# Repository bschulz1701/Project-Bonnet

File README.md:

# Project-Bonnet
Compact, self contained, multi-point voltage logger/monitor. Designed for use as a testing device.

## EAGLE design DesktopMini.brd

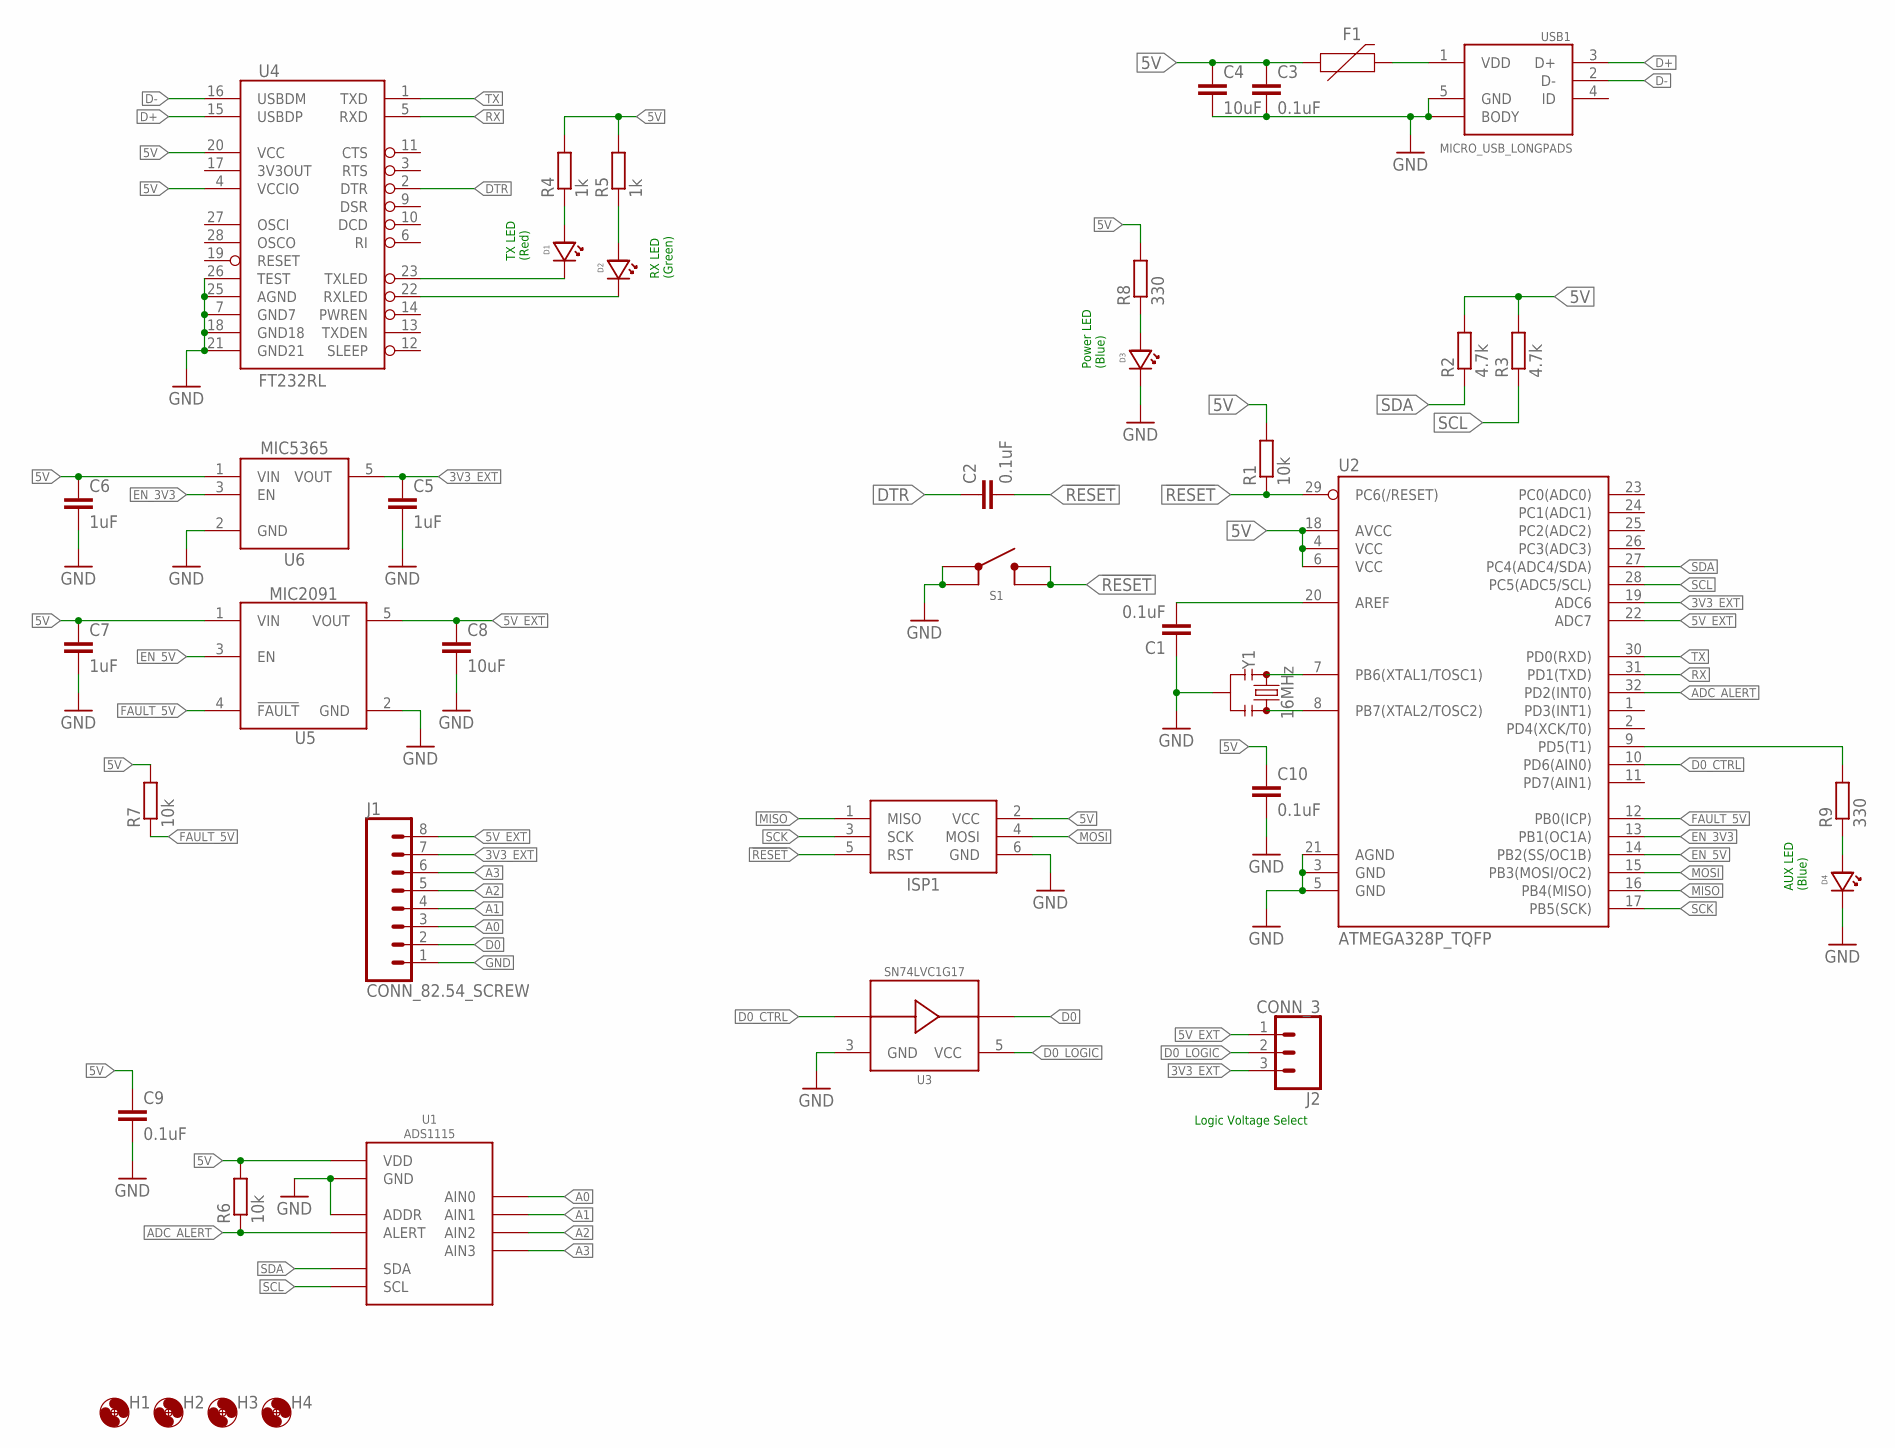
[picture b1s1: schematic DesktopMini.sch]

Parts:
C1, C2, C3, C9, C10: 0.1uF; C0603
C4, C8: 10uF; C0805
C5, C6, C7: 1uF; C0603
D1: LEDRED0603; LED_0603
D2: LEDGREEN0603; LED_0603
D3, D4: LEDBLUE0603; LED_0603
F1: PPTC_HALF-AMP; 1206
H1, H2, H3, H4: MOUNTING_HOLE4_NP; 4_40
ISP1: AVRISP-6; AVRISP
J1: CONN_82.54_SCREW; 1X08_SCREW
J2: CONN_3; 1X03
R1, R6, R7: 10k; R0603
R2, R3: 4.7k; R0603
R4, R5: 1k; R0603
R8, R9: 330; R0603
S1: BUTTON6X6; SWITCH_6MM
U1: ADS1115; VSSOP_10
U2: ATMEGA328P_TQFP; TQFP32-08
U3: SN74LVC1G17DCK; DCK_R-PDSO-G5
U4: FT232RL; SSOP28DB
U5: MIC2091; SOT23-5
U6: MIC53653.3SC70; DCK_R-PDSO-G5
USB1: MICRO_USB_LONGPADS; 10118194-0001LF_10118194-0001LF_LONGER_PADS
Y1: 16MHz; RESONATOR-SMD-3.2X1.3

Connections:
3V3_EXT: C5.1, J1.7, J2.3, U2.19 (ADC6), U6.5 (VOUT)
5V: C3.1, C4.1, C6.1, C7.1, C9.1, C10.1, F1.1, ISP1.2 (VCC), R1.2, R2.2, R3.2, R4.2, R5.2, R6.2, R7.2, R8.2, U1.8 (VDD), U2.4 (VCC), U2.6 (VCC), U2.18 (AVCC), U4.4 (VCCIO), U4.20 (VCC), U5.1 (VIN), U6.1 (VIN)
5V_EXT: C8.1, J1.8, J2.1, U2.22 (ADC7), U5.5 (VOUT)
!RESET: C2.2, ISP1.5 (RST), R1.1, S1.3, S1.4, U2.29 (PC6(/RESET))
A0: J1.3, U1.4 (AIN0)
A1: J1.4, U1.5 (AIN1)
A2: J1.5, U1.6 (AIN2)
A3: J1.6, U1.7 (AIN3)
ADC_ALERT: R6.1, U1.2 (ALERT), U2.32 (PD2(INT0))
AUX_LED: R9.2, U2.9 (PD5(T1))
D0: J1.2, U3.4 (Y)
D0_CTRL: U2.10 (PD6(AIN0)), U3.2 (A)
D0_LOGIC: J2.2, U3.5 (VCC)
D+: U4.15 (USBDP), USB1.3 (D+)
D-: U4.16 (USBDM), USB1.2 (D-)
DTR: C2.1, U4.2 (DTR)
EN_3V3: U2.13 (PB1(OC1A)), U6.3 (EN)
EN_5V: U2.14 (PB2(SS/OC1B)), U5.3 (EN)
FAULT_5V: R7.1, U2.12 (PB0(ICP)), U5.4 (!FAULT)
GND: C1.1, C3.2, C4.2, C5.2, C6.2, C7.2, C8.2, C9.2, C10.2, D3.CATHODE, D4.CATHODE, ISP1.6 (GND), J1.1, S1.1, S1.2, U1.1 (ADDR), U1.3 (GND), U2.3 (GND), U2.5 (GND), U2.21 (AGND), U3.3 (GND), U4.7 (GND7), U4.18 (GND18), U4.21 (GND21), U4.25 (AGND), U4.26 (TEST), U5.2 (GND), U6.2 (GND), USB1.5 (GND), USB1.BODY@1 (BODY), USB1.BODY@2 (BODY), USB1.BODY@3 (BODY), USB1.BODY@4 (BODY), USB1.BODY@7 (BODY), USB1.BODY@8 (BODY), Y1.2
MISO: ISP1.1 (MISO), U2.16 (PB4(MISO))
MOSI: ISP1.4 (MOSI), U2.15 (PB3(MOSI/OC2))
unnamed: U2.7 (PB6(XTAL1/TOSC1)), Y1.1
unnamed: U2.8 (PB7(XTAL2/TOSC2)), Y1.3
unnamed: C1.2, U2.20 (AREF)
unnamed: D1.ANODE, R4.1
unnamed: F1.2, USB1.1 (VDD)
unnamed: D2.ANODE, R5.1
unnamed: D1.CATHODE, U4.23 (TXLED)
unnamed: D2.CATHODE, U4.22 (RXLED)
unnamed: D3.ANODE, R8.1
unnamed: D4.ANODE, R9.1
RX: U2.31 (PD1(TXD)), U4.5 (RXD)
SCK: ISP1.3 (SCK), U2.17 (PB5(SCK))
SCL: R3.1, U1.10 (SCL), U2.28 (PC5(ADC5/SCL))
SDA: R2.1, U1.9 (SDA), U2.27 (PC4(ADC4/SDA))
TX: U2.30 (PD0(RXD)), U4.1 (TXD)

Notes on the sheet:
Power LED (Blue)
TX LED (Red)
RX LED (Green)
Logic Voltage Select
AUX LED (Blue)

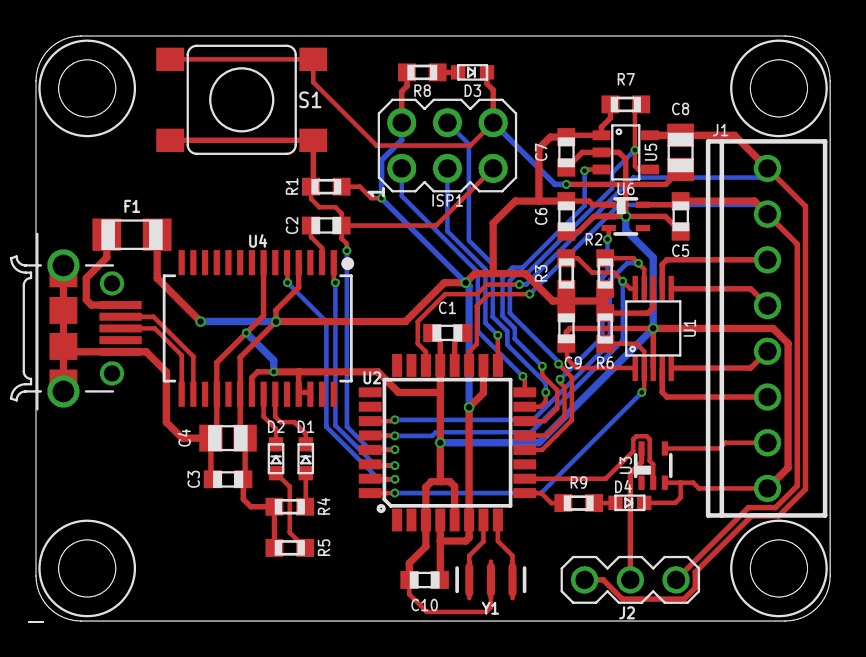
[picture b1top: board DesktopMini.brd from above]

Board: 2 copper layers, 44.1 x 32.5 mm, 40 parts (0 on the bottom side), 37 nets.

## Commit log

2020-06-23 Initial Dev, review required
    First round of layout completed, needs review and minor cleanup
2020-06-23 Added license
2020-06-24 Minor updates, v0.0 to fab
    Added auxiliary LED and did minor cleanup, added BMP image via script

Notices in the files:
parts and their libraries:
bschulz: This work is licensed under the Creative Commons Attribution-ShareAlike 4.0
http://creativecommons.org/licenses/by-sa/4.0
